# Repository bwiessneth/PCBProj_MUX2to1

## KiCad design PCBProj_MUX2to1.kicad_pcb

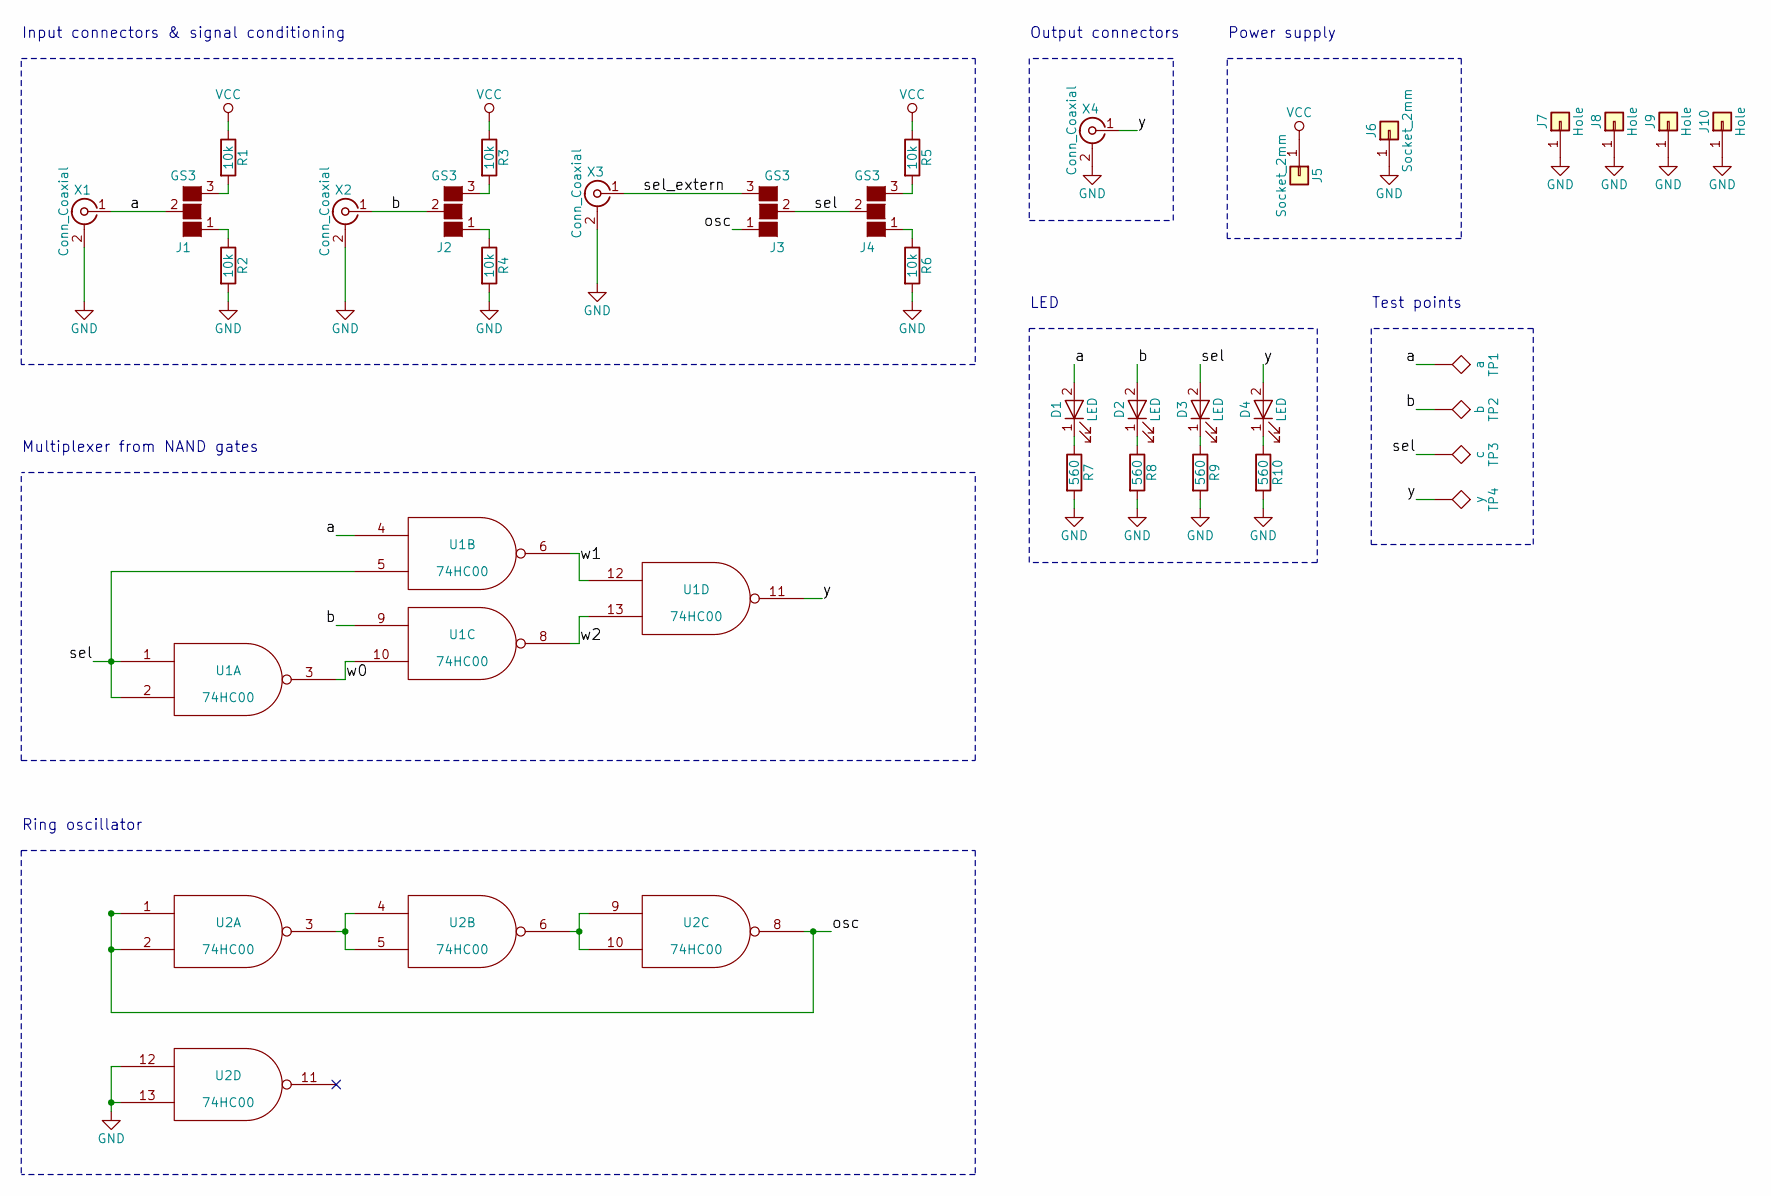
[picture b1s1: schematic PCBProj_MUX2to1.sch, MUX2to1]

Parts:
D1, D2, D3, D4: LED; LED_0805_HandSoldering
J1, J2, J3, J4: GS3; Pin_Header_Straight_1x03_Pitch2.54mm
J5, J6: Socket_2mm; Conn_Socket_2mm_LB2-A
J7, J8, J9, J10: Hole; MountingHole_6mm_Pad
R1, R2, R3, R4, R5, R6: 10k; R_0805_HandSoldering
R7, R8, R9, R10: 560; R_0805_HandSoldering
TP1: a; TestPoint_Pin_1mm
TP2: b; TestPoint_Pin_1mm
TP3: c; TestPoint_Pin_1mm
TP4: y; TestPoint_Pin_1mm
U1, U2: 74HC00; dil_14-300_socket
X1, X2, X3, X4: Conn_Coaxial; BNC_Connector_Angled

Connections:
/a: D1.2 (A), J1.2 (G2), TP1.1, U1.4, X1.1 (In)
/b: D2.2 (A), J2.2 (G2), TP2.1, U1.9, X2.1 (In)
/osc: J3.1 (G1), U2.1, U2.2, U2.8
/sel: D3.2 (A), J3.2 (G2), J4.2 (G2), TP3.1, U1.1, U1.2, U1.5
/sel_extern: J3.3 (G3), X3.1 (In)
/w0: U1.3, U1.10
/w1: U1.6, U1.12
/w2: U1.8, U1.13
/y: D4.2 (A), TP4.1, U1.11, X4.1 (In)
GND: J6.1, J7.1, J8.1, J9.1, J10.1, R2.2, R4.2, R6.2, R7.2, R8.2, R9.2, R10.2, U1.7 (GND), U2.7 (GND), U2.12, U2.13, X1.2 (Ext), X2.2 (Ext), X3.2 (Ext), X4.2 (Ext)
unnamed: D1.1 (K), R7.1
unnamed: D2.1 (K), R8.1
unnamed: D3.1 (K), R9.1
unnamed: D4.1 (K), R10.1
unnamed: J1.1 (G1), R2.1
unnamed: J1.3 (G3), R1.2
unnamed: J2.1 (G1), R4.1
unnamed: J2.3 (G3), R3.2
unnamed: J4.1 (G1), R6.1
unnamed: J4.3 (G3), R5.2
unnamed: U2.3, U2.4, U2.5
unnamed: U2.6, U2.9, U2.10
VCC: J5.1, R1.1, R3.1, R5.1, U1.14 (VCC), U2.14 (VCC)

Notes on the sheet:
Input connectors & signal conditioning
Output connectors
LED
Multiplexer from NAND gates
Ring oscillator
Power supply
Test points

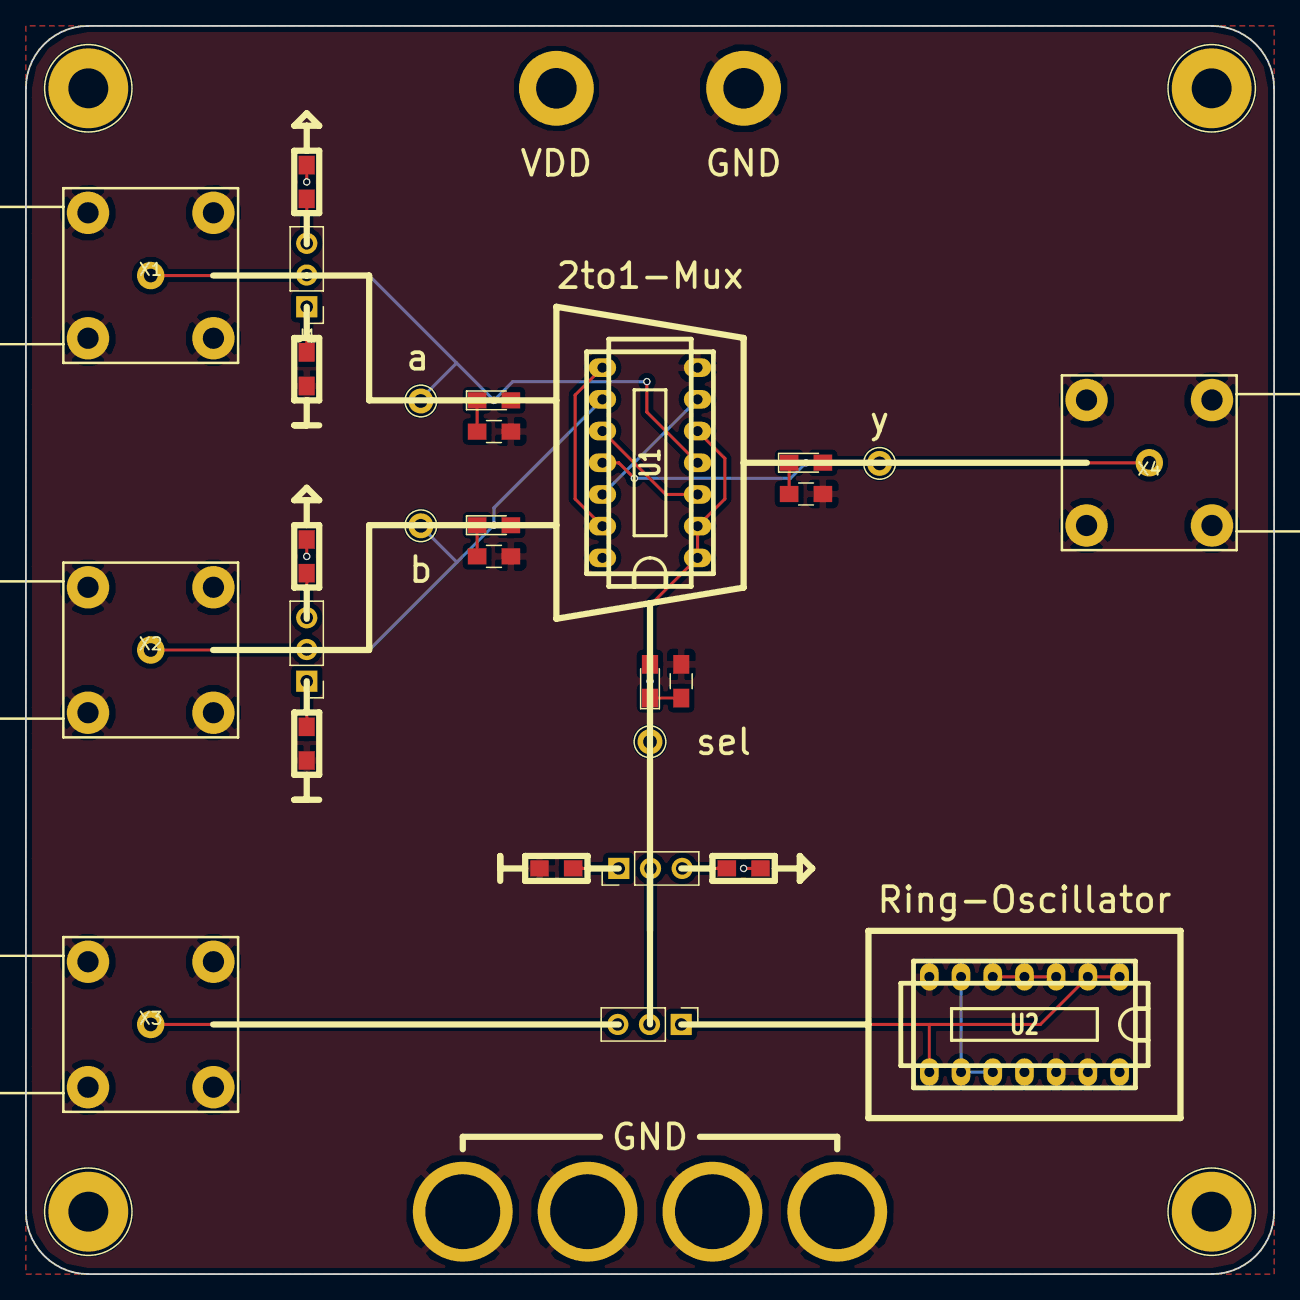
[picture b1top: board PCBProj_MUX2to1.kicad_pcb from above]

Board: 2 copper layers, 100.0 x 100.0 mm, 34 parts (0 on the bottom side), 23 nets.

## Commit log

2018-01-07 Added holes for GND probes
2018-01-07 Updated preview
